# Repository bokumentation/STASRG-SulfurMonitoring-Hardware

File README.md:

# Init Main Branch

clone this repo with the submodules

```
git clone --recursive https://github.com/bokumentation/STASRG-SulfurMonitoring-Hardware.git
```

## to-do-list

- memisahkan firmware dari repo ini
    - receiver
    - transmitter
    - dummy-uart
- membuat repo sendiri libs untuk kicad dan dibuat submodules

# ghostl + ESP32-S3: The `-mtext-section-literals` Fix

## The Problem

Building ESP-IDF projects that use `ghostl` (via `espsoftwareserial`) for **ESP32-S3** fails with:

```
dangerous relocation: l32r: literal placed after use: .literal._ZNK8delegate...
```

This error **does not** occur on:
- **ESP32** (Xtensa LX6)
- **ESP32-C3** (RISC-V)

And it **does not** occur when building the same code with **Arduino IDE** (arduino-esp32).

## Root Cause

### The `l32r` instruction

The Xtensa architecture has a `l32r` (load literal from PC-relative) instruction used to load 32-bit constants. It loads a value from a **literal pool** — a table of constants placed at a known offset from the current PC. The range of `l32r` is approximately ±256 KB from the instruction.

### IRAM vs Flash on ESP32-S3

Functions marked with `IRAM_ATTR` (as many are in `Delegate.h` and `SoftwareSerial`) are placed in **IRAM** (internal RAM, address range 0x4037xxxx). The normal code (.text) is placed in **flash** (mapped to 0x4200xxxx).

Without `-mtext-section-literals`:
- The compiler places all literal pools in a **centralized .literal section** that lives alongside the flash code (0x4200xxxx)
- Functions in IRAM emit `l32r` instructions pointing to the .literal section in flash
- The distance between IRAM (0x4037xxxx) and the literal pool in flash (0x4200xxxx) exceeds the `l32r` addressing range
- The linker rejects this as a **dangerous relocation**

### Why ESP32 (LX6) is fine

ESP32 uses Xtensa LX6 which defaults to **`-mtext-section-literals` being enabled** in ESP-IDF. So the literal pool is placed inside each text section — no cross-section addressing issue.

### Why ESP32-C3 (RISC-V) is fine

ESP32-C3 is RISC-V, not Xtensa. It has no `l32r` instruction — it uses a different instruction encoding for loading constants. The issue is Xtensa-specific.

### Why Arduino IDE is fine

Arduino IDE (arduino-esp32) sets compile flags differently than ESP-IDF. In particular, it passes `-mtext-section-literals` by default in its platform configuration, avoiding the problem entirely. This is why the same source code that fails in ESP-IDF works in Arduino without any modifications.

## The Fix: `-mtext-section-literals`

Add this to the `CMakeLists.txt` of any component that depends on `ghostl` (e.g. `espsoftwareserial`):

```cmake
target_compile_options(${COMPONENT_LIB} PRIVATE -mtext-section-literals)
```

### How it works

The `-mtext-section-literals` flag tells the Xtensa compiler to place each function's literal pool **inside that function's own text section**, rather than in a centralized `.literal` section. Since the function is in IRAM, its literals go to IRAM too — well within `l32r` range.

### Is it safe?

**Yes, it is completely safe:**

| Concern | Assessment |
|---|---|
| Runtime behavior | No functional change. Literals are read-only constants — being in IRAM vs flash makes no difference to program correctness. |
| Performance | No impact. Constants are read the same way via cache at full speed. |
| IRAM / ISR usage | Preserved. All `IRAM_ATTR` functions continue to work correctly in interrupt context. |
| Binary size | Minor increase (typically < 1 KB). Literal pools may be duplicated across functions instead of shared, but this is negligible. |
| Espressif recommendation | Standard practice. Used by default on ESP32 and in Arduino-esp32. |

## The Previous Attempt: Removing `IRAM_ATTR`

### What we tried

We removed `IRAM_ATTR` from the `operator()` methods in `DelegatePImpl` and `DelegateImpl` classes (the `std::function`/`FUNC` path) in `Delegate.h`.

### Why it worked

Without `IRAM_ATTR`, those functions are placed in flash (0x4200xxxx), right next to the centralized `.literal` section. The `l32r` instruction can reach the literal pool fine — same section, same address space.

### Why we reverted it

Removing `IRAM_ATTR` means those functions **cannot be called from ISR context** — a fundamental requirement for software serial implementations where UART callbacks happen in interrupt context. The `FP` and `FPA` dispatch paths (raw function pointers) retained `IRAM_ATTR`, but the `std::function` path lost ISR safety.

### The better solution

Instead of modifying source code (and compromising ISR safety), we use `-mtext-section-literals` which requires **zero source changes**. All dispatch paths keep their `IRAM_ATTR`, all functions stay ISR-safe, and the linker error is resolved at the compiler flag level.

## Summary

| Build Environment | Default `-mtext-section-literals` | Builds? |
|---|---|---|
| ESP-IDF + ESP32 | ✅ Yes (default) | ✅ |
| ESP-IDF + ESP32-C3 | N/A (RISC-V, no l32r) | ✅ |
| ESP-IDF + ESP32-S3 | ❌ No (default) | ❌ Fails |
| Arduino IDE + ESP32-S3 | ✅ Yes (in platform config) | ✅ |

The fix: add `-mtext-section-literals` to the consumer component's CMakeLists.txt. No source code changes needed.

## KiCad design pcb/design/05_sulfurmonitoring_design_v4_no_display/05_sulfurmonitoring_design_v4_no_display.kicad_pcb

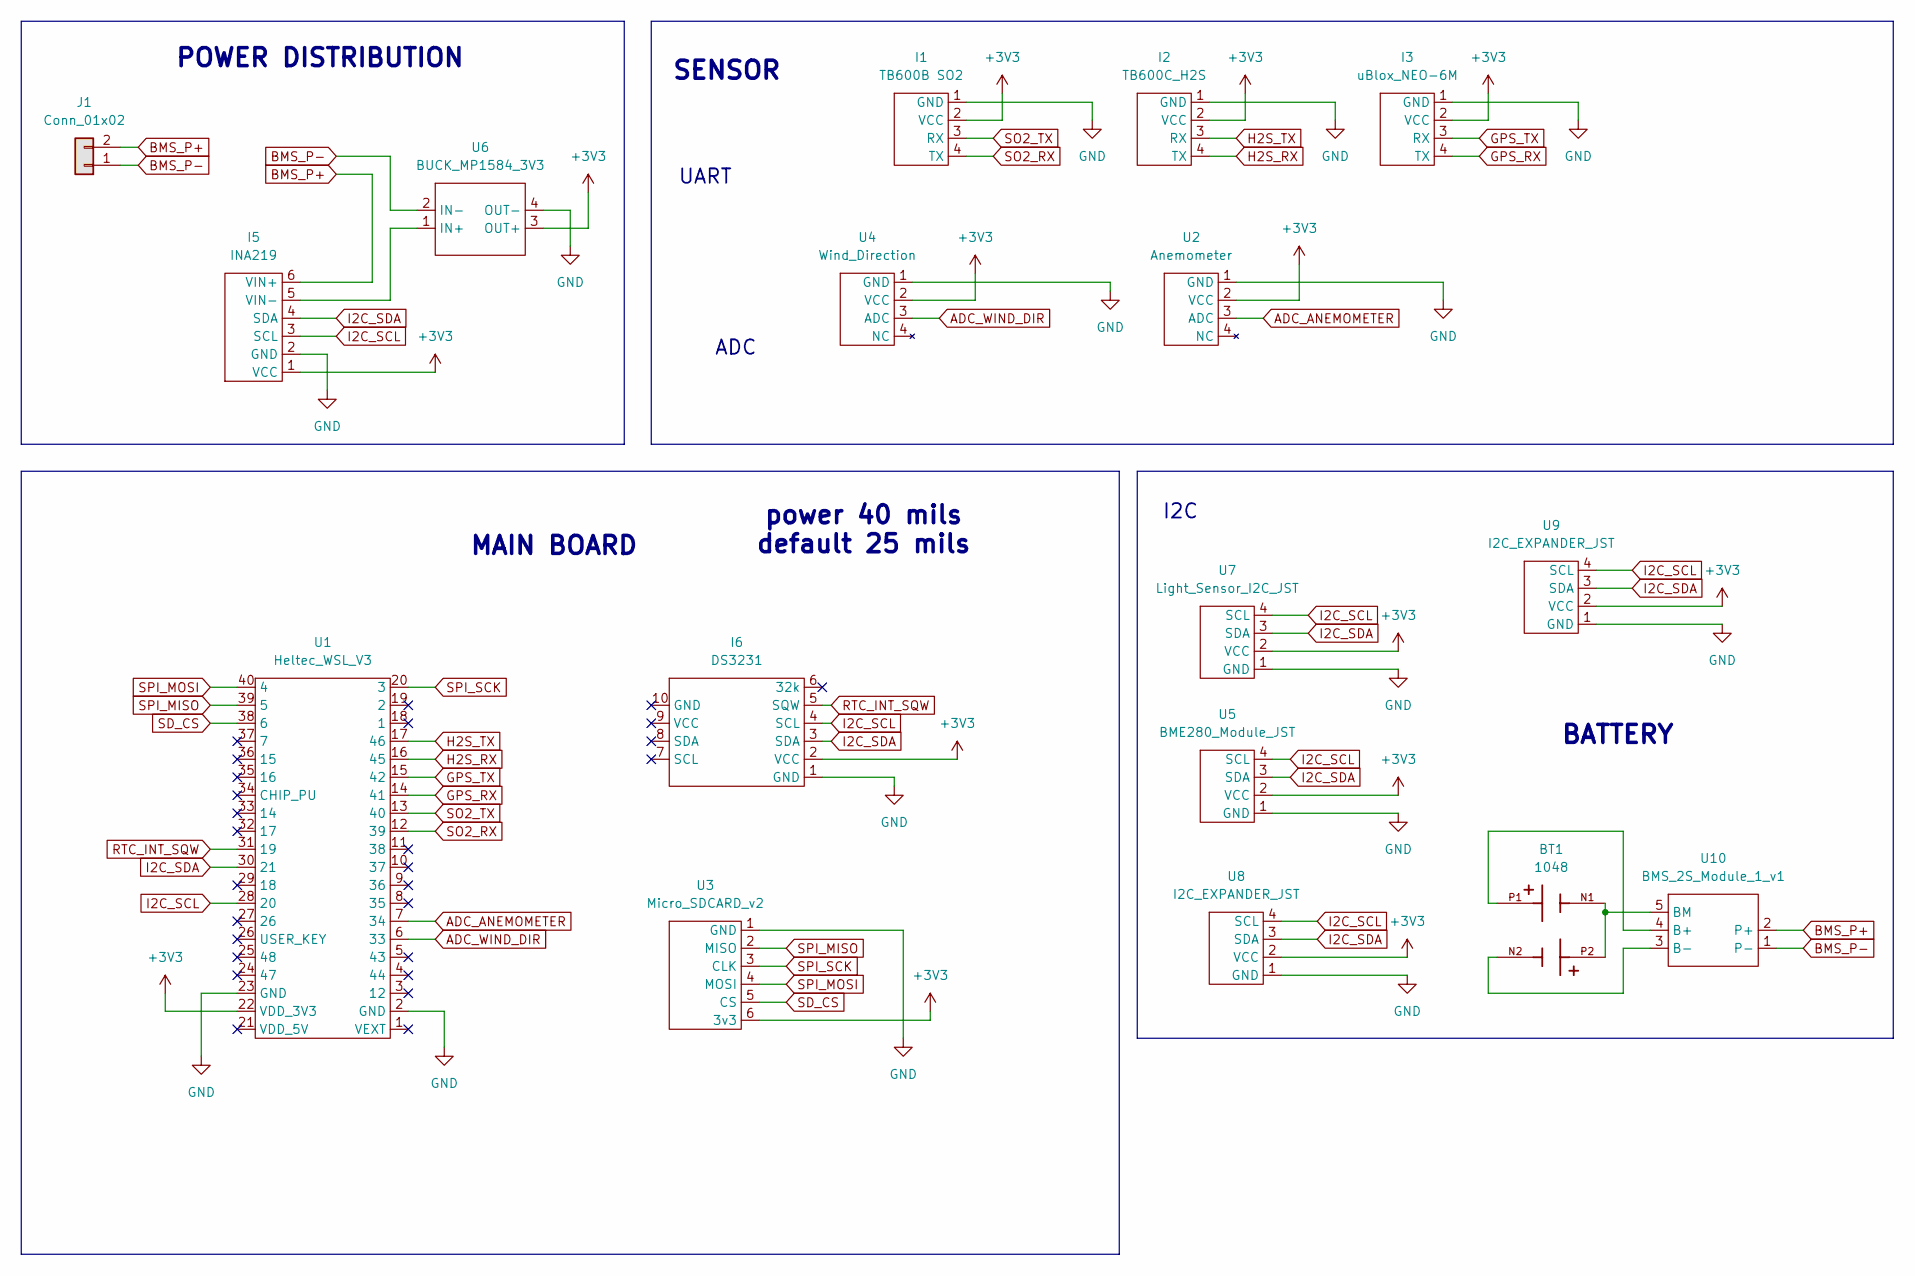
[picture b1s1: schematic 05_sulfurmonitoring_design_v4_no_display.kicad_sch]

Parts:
BT1: 1048; BAT_1048; PARTREV A; DigiKey_Part_Number 36-1048-ND
I1: TB600B SO2; TB600B_SO2_Module
I2: TB600C_H2S; TB600C_H2S_Module
I3: uBlox_NEO-6M; uBlox_NEO-6M_Module_JST
I5: INA219; INA219_Module
I6: DS3231​; DS3231_Module
J1: Conn_01x02; JST_XH_B2B-XH-A_1x02_P2.50mm_Vertical
U1: Heltec_WSL_V3; Heltec_WSL_V3_Module
U2: Anemometer; STASRG_Anemometer_Module
U3: Micro_SDCARD_v2; Micro_SDCARD_v2_Module
U4: Wind_Direction; STASRG_Wind_Dir_Module
U5: BME280_Module_JST; JST_XH_B4B-XH-A_1x04_P2.50mm_Vertical
U6: BUCK_MP1584_3V3; BUCK_MP1584_3V3_Module
U7: Light_Sensor_I2C_JST; JST_XH_B4B-XH-A_1x04_P2.50mm_Vertical
U8, U9: I2C_EXPANDER_JST; JST_XH_B4B-XH-A_1x04_P2.50mm_Vertical
U10: BMS_2S_Module_1_v1

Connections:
+3V3: I1.2 (VCC), I2.2 (VCC), I3.2 (VCC), I5.1 (VCC), I6.2 (VCC), U1.22 (VDD_3V3), U2.2 (VCC), U3.6 (3v3), U4.2 (VCC), U5.2 (VCC), U6.3 (OUT+), U7.2 (VCC), U8.2 (VCC), U9.2 (VCC)
ADC_ANEMOMETER: U1.7 (34), U2.3 (ADC)
ADC_WIND_DIR: U1.6 (33), U4.3 (ADC)
BMS_P+: I5.6 (VIN+), J1.2, U10.2 (P+); also elsewhere on the board
BMS_P-: J1.1, U6.2 (IN-), U10.1 (P-); also elsewhere on the board
GND: I1.1 (GND), I2.1 (GND), I3.1 (GND), I5.2 (GND), I6.1 (GND), U1.2 (GND), U1.23 (GND), U2.1 (GND), U3.1 (GND), U4.1 (GND), U5.1 (GND), U6.4 (OUT-), U7.1 (GND), U8.1 (GND), U9.1 (GND)
GPS_RX: I3.4 (TX), U1.14 (41)
GPS_TX: I3.3 (RX), U1.15 (42)
H2S_RX: I2.4 (TX), U1.16 (45)
H2S_TX: I2.3 (RX), U1.17 (46)
I2C_SCL: I5.3 (SCL), I6.4 (SCL), U1.28 (20), U5.4 (SCL), U7.4 (SCL), U8.4 (SCL), U9.4 (SCL)
I2C_SDA: I5.4 (SDA), I6.3 (SDA), U1.30 (21), U5.3 (SDA), U7.3 (SDA), U8.3 (SDA), U9.3 (SDA)
unnamed: I5.5 (VIN-), U6.1 (IN+)
unnamed: BT1.P1, U10.4 (B+)
unnamed: BT1.N2, U10.3 (B-)
unnamed: BT1.N1, BT1.P2, U10.5 (BM)
RTC_INT_SQW: I6.5 (SQW), U1.31 (19)
SD_CS: U1.38 (6), U3.5 (CS)
SO2_RX: I1.4 (TX), U1.12 (39)
SO2_TX: I1.3 (RX), U1.13 (40)
SPI_MISO: U1.39 (5), U3.2 (MISO)
SPI_MOSI: U1.40 (4), U3.4 (MOSI)
SPI_SCK: U1.20 (3), U3.3 (CLK)

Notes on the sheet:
BATTERY
UART
I2C
ADC
POWER DISTRIBUTION
power 40 mils default 25 mils
SENSOR
MAIN BOARD

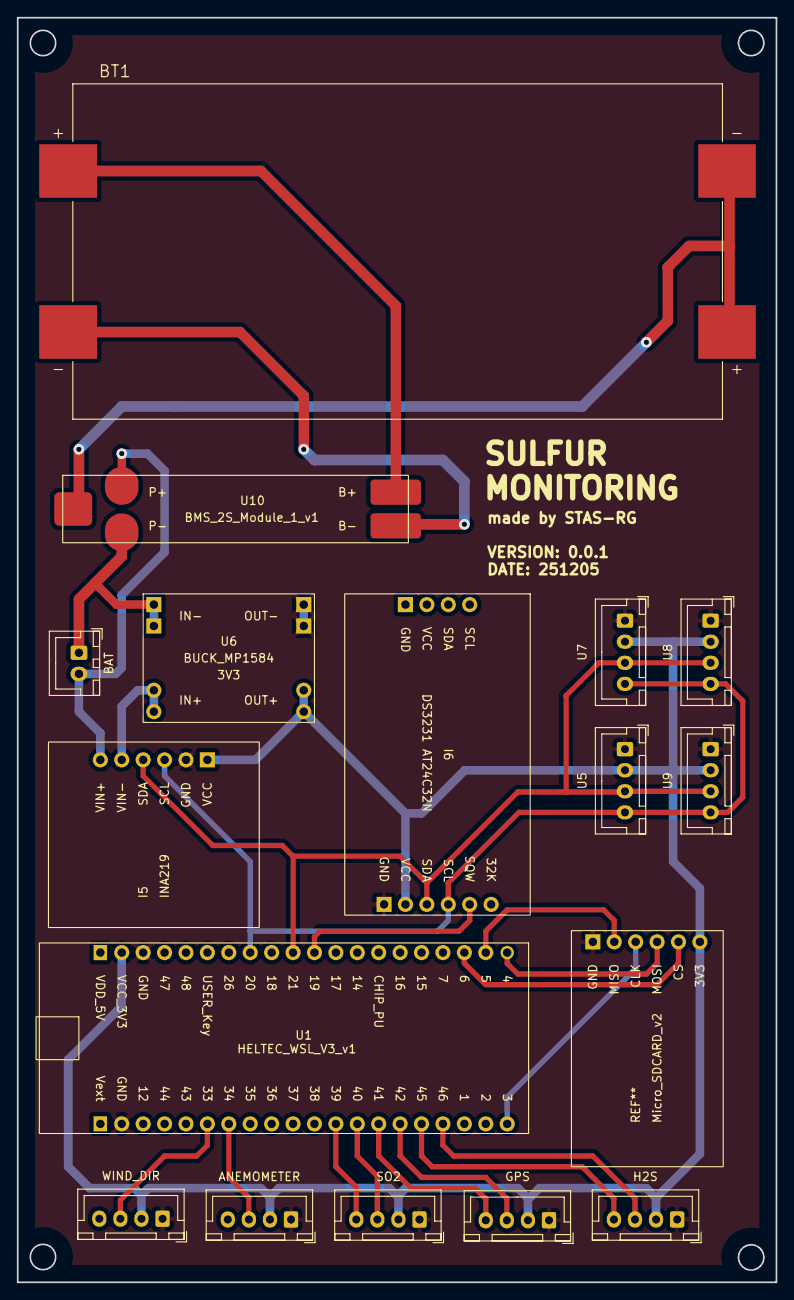
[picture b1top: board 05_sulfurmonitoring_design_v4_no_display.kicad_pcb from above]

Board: 2 copper layers, 90.0 x 150.0 mm, 17 parts (0 on the bottom side), 23 nets.

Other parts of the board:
BAT: Conn_01x02; JST_XH_B2B-XH-A_1x02_P2.50mm_Vertical

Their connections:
BMS_P+: BAT.2; also elsewhere on the board
BMS_P-: BAT.1; also elsewhere on the board

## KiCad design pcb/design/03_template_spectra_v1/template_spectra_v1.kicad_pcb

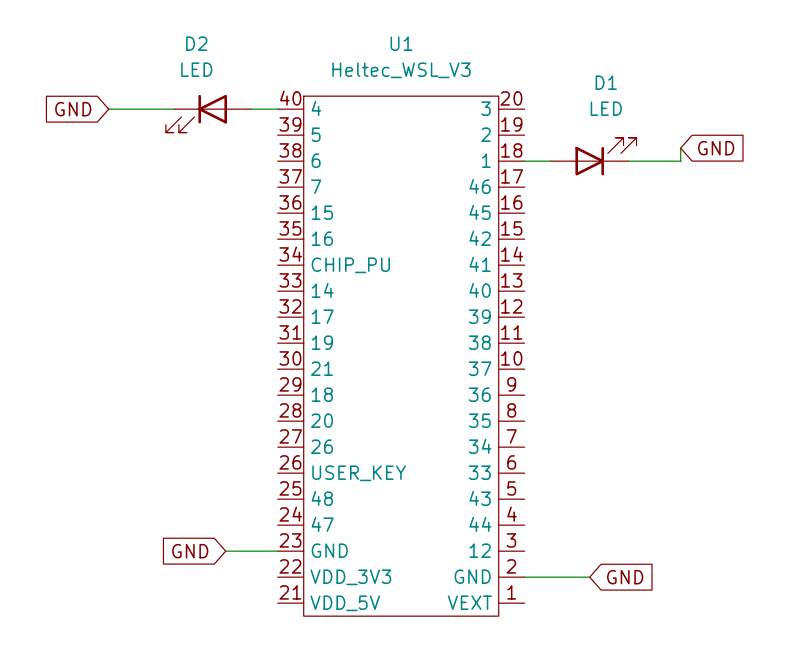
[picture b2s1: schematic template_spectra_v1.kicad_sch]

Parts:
D1, D2: LED; LED_D5.0mm
U1: Heltec_WSL_V3; Heltec_WSL_V3_v1

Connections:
GND: D1.1 (K), D2.1 (K), U1.2 (GND), U1.23 (GND)
unnamed: D1.2 (A), U1.18 (1)
unnamed: D2.2 (A), U1.40 (4)

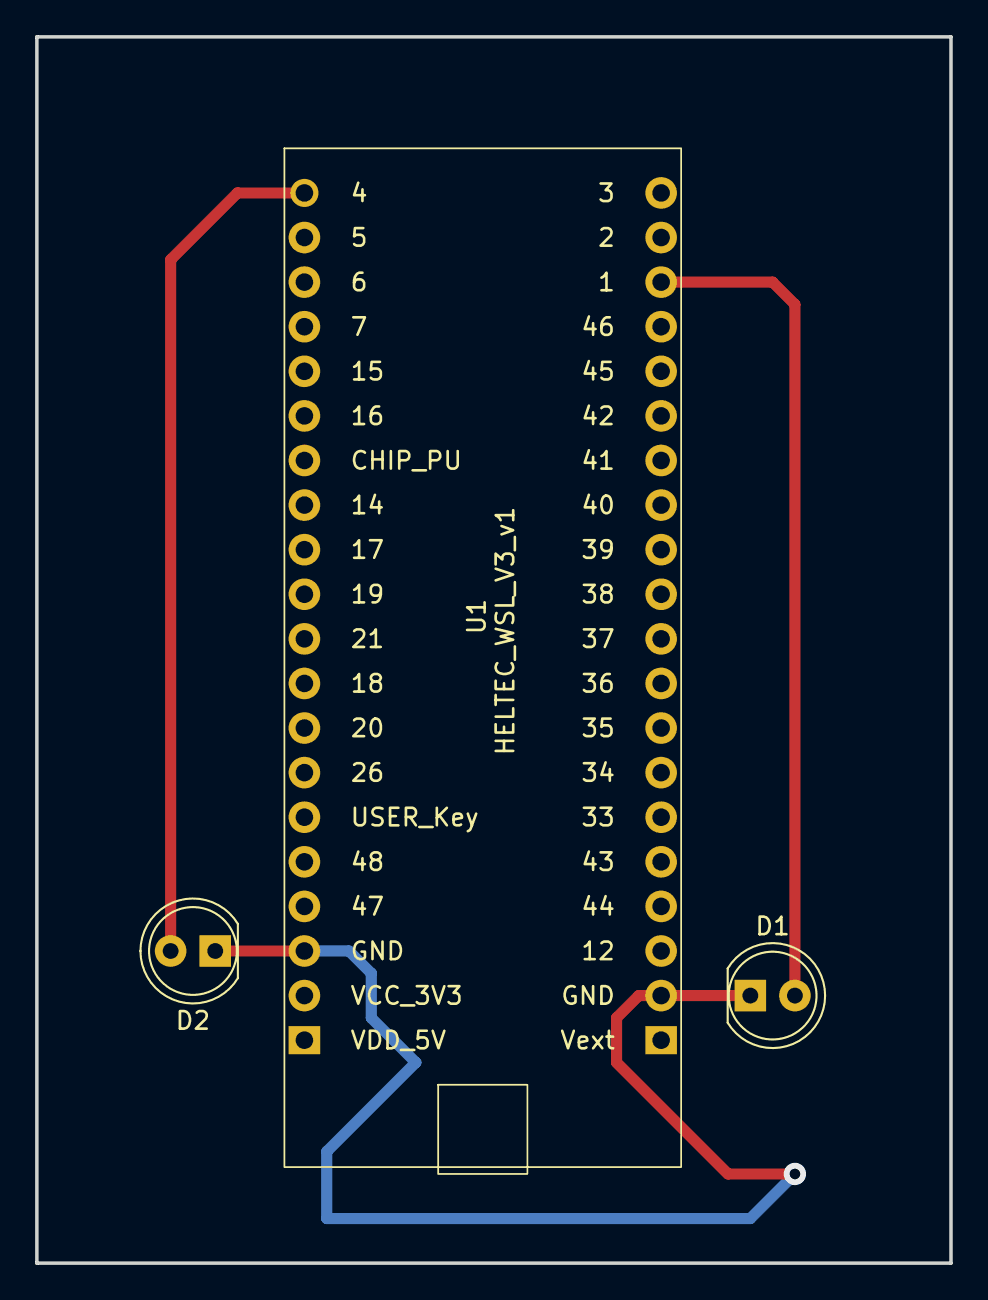
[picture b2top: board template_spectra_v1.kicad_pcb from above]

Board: 2 copper layers, 52.1 x 69.8 mm, 3 parts (0 on the bottom side), 3 nets.

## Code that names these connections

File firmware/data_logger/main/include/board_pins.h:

#ifndef BOARD_PINS_H
#define BOARD_PINS_H

#include <sdkconfig.h>
#include <hal/gpio_hal.h>

// Define Board Type. If you use HELTEC Wireless Stick Lite, please uncomment it.
// #define BOARD_DEVKITC_ESP32S3_V1
#define BOARD_HELTEC_WSL_ESP32S3_V3

#ifdef CONFIG_IDF_TARGET_ESP32
    #define ANEMOMETER_ADC_PIN GPIO_NUM_32

    #define H2S_UART_PORT UART_NUM_1
    #define H2S_RX_PIN GPIO_NUM_26
    #define H2S_TX_PIN GPIO_NUM_27
    #define H2S_LOG_TAG "TB600B_H2S"

    #define SO2_UART_PORT UART_NUM_2
    #define SO2_RX_PIN GPIO_NUM_16
    #define SO2_TX_PIN GPIO_NUM_17
    #define SO2_LOG_TAG "TB600B_SO2"

#elif defined(CONFIG_IDF_TARGET_ESP32C3)
    #define ANEMOMETER_ADC_PIN GPIO_NUM_3

    #define H2S_UART_PORT UART_NUM_0
    #define H2S_RX_PIN GPIO_NUM_9
    #define H2S_TX_PIN GPIO_NUM_10
    #define H2S_LOG_TAG "TB600B_H2S"

    #define SO2_UART_PORT UART_NUM_1
    #define SO2_RX_PIN GPIO_NUM_20
    #define SO2_TX_PIN GPIO_NUM_21
    #define SO2_LOG_TAG "TB600B_SO2"

#elif defined(CONFIG_IDF_TARGET_ESP32S3)
    #if defined(BOARD_DEVKITC_ESP32S3_V1)
        #define ANEMOMETER_ADC_PIN GPIO_NUM_3

        #define SO2_UART_PORT UART_NUM_0
        #define SO2_RX_PIN GPIO_NUM_44
        #define SO2_TX_PIN GPIO_NUM_43
        #define SO2_LOG_TAG "TB600B_SO2"

        #define H2S_UART_PORT UART_NUM_1
        #define H2S_RX_PIN GPIO_NUM_17
        #define H2S_TX_PIN GPIO_NUM_18
        #define H2S_LOG_TAG "TB600B_H2S"

    #elif defined(BOARD_HELTEC_WSL_ESP32S3_V3)
        // - 0. LoRa SX1262 PINS (FIXED by Heltec WSL v3) ---
        // These pins are hardwired to the onboard HELTEC LoRa module.
        #define PIN_LORA_NSS        8
        #define PIN_LORA_SCK        9
        #define PIN_LORA_MISO       10
        #define PIN_LORA_MOSI       11
        #define PIN_LORA_RST        12
        #define PIN_LORA_BUSY       13
        #define PIN_LORA_DIO1       14

        // - 1. SPI BUS (SD Card and W5500 Ethernet) ---
        // -- 1.1 Dedicated SPI bus (SPI3/VSPI) using accessible GPIO pins
        #define PIN_SPI3_SCK         3
        #define PIN_SPI3_MOSI        4
        #define PIN_SPI3_MISO        5
        // -- 1.2 Select Pin for SPI3 connected modules
        #define PIN_SD_CS           6     
        #define PIN_W5500_CS        2

        // - 2. I2C BUS (RTC, OLED, INA219 x2) ---
        #define PIN_I2C_SCL         20
        #define PIN_I2C_SDA         21
        // -- 2.1. I2C ADDRESS for the modules ---
        #define ADDR_DS3231_RTC
        #define ADDR_SSD1306_DISPLAY
        #define ADDR_INA219_SENSOR_1
        #define ADDR_INA219_SENSOR_2
        // -- 2.2. Additional Control PIN ---
        #define PIN_RTC_INT_SQW     19

        // - 3. UART PERIPHERALS (Sensors and GPS) ---      
        // -- 3.1. UART 1 (Hardware) - TB600B H2S Sensor: ✅ TESTED
        #define SENSOR_H2S_UART_PORT UART_NUM_1
        #define SENSOR_H2S_TAG "TB600B_H2S"
        #define PIN_H2S_TX          17  // YELLOW
        #define PIN_H2S_RX          18  // WHITE
        // -- 3.2. UART 2 (Hardware) - TB600B SO2 Sensor: ✅ TESTED
        #define SENSOR_SO2_UART_PORT UART_NUM_2
        #define SENSOR_SO2_TAG "TB600B_SO2"
        #define PIN_SO2_TX          40  // YELLO
        #define PIN_SO2_RX          39  // WHITE
        // -- 3.3. UART GPS Module uses Software Serial
        #define PIN_GPS_TX          42
        #define PIN_GPS_RX          41

        // - 4. ANALOG (ADC) Inputs (Wind Speed and Sirection) ---
        #define PIN_ANEMOMETER_ADC  34 // ADC1_CH3
        #define PIN_WIND_DIR_ADC    33 // ADC1_CH4
    #endif
#else
    #error "Unsupported IDF_TARGET! Please set the target using idf.py set-target."

#endif // CONFIG_IDF_TARGET

#define BAUD_RATE 9600

#endif // BOARD_PINS_H

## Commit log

2025-11-23 init
2025-11-23 deteled resources
2025-11-23 added tools
2025-11-27 Added Test
2025-11-27 added new arduino as components
2025-11-28 Create Symbols
    Symbols and Footprints
2025-11-28 Create Syms and Footp
2025-12-01 added module references
2025-12-01 Added PCB Module References
2025-12-01 edit some footprint
2025-12-01 edit f. courtyard
2025-12-01 renamed symbol to libraries
2025-12-01 deleted footprint folder
2025-12-01 renamed and added test library
2025-12-01 added new design
2025-12-01 design
2025-12-01 added revision
2025-12-02 update design
2025-12-05 update drc
2025-12-07 new design
2025-12-08 added output gerber
2025-12-08 added and remove some components
2025-12-09 added some adjusment
2025-12-09 added sensor_task
2025-12-14 added new test
2025-12-16 added new componetns
2025-12-17 Update for esp32s3 target
    Added ANEMOMETER_TAG
    Using PIN_SENSOR_ANEMOMETER_ADC
2025-12-21 Update added some library
2025-12-21 addeed library
2025-12-21 edit cmakelists.txt
2026-01-07 added new components
2026-01-09 Update dokumentasi
2026-04-25 big changes
2026-04-25 edit pcb
2026-04-25 add new submodules
2026-04-25 Update ignore
2026-04-25 add changelog
2026-04-25 add new info
2026-04-25 Pointing to new test commit
